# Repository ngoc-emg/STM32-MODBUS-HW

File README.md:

# STM32-MODBUS-HW
STM32-MODBUS HW

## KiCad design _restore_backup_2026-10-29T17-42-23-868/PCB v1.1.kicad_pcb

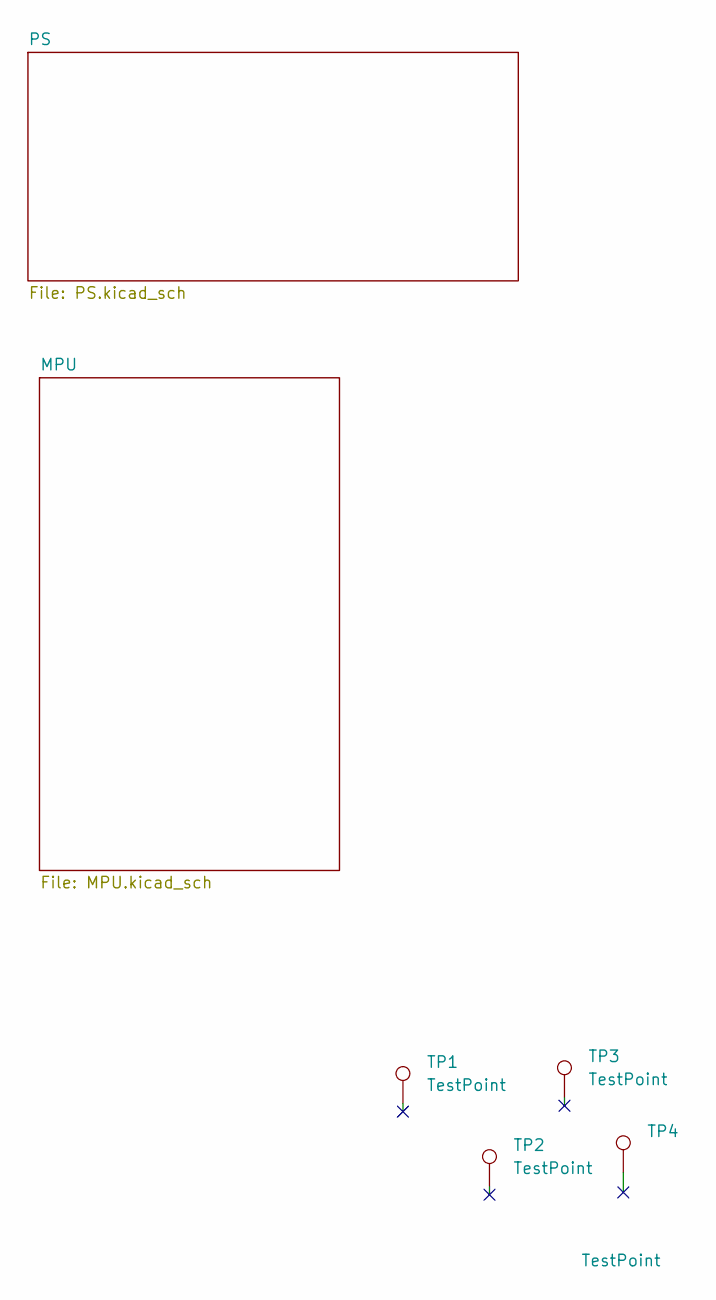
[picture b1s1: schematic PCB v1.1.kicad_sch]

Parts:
TP1, TP2, TP3, TP4: TestPoint; TestPoint_Plated_Hole_D4.0mm

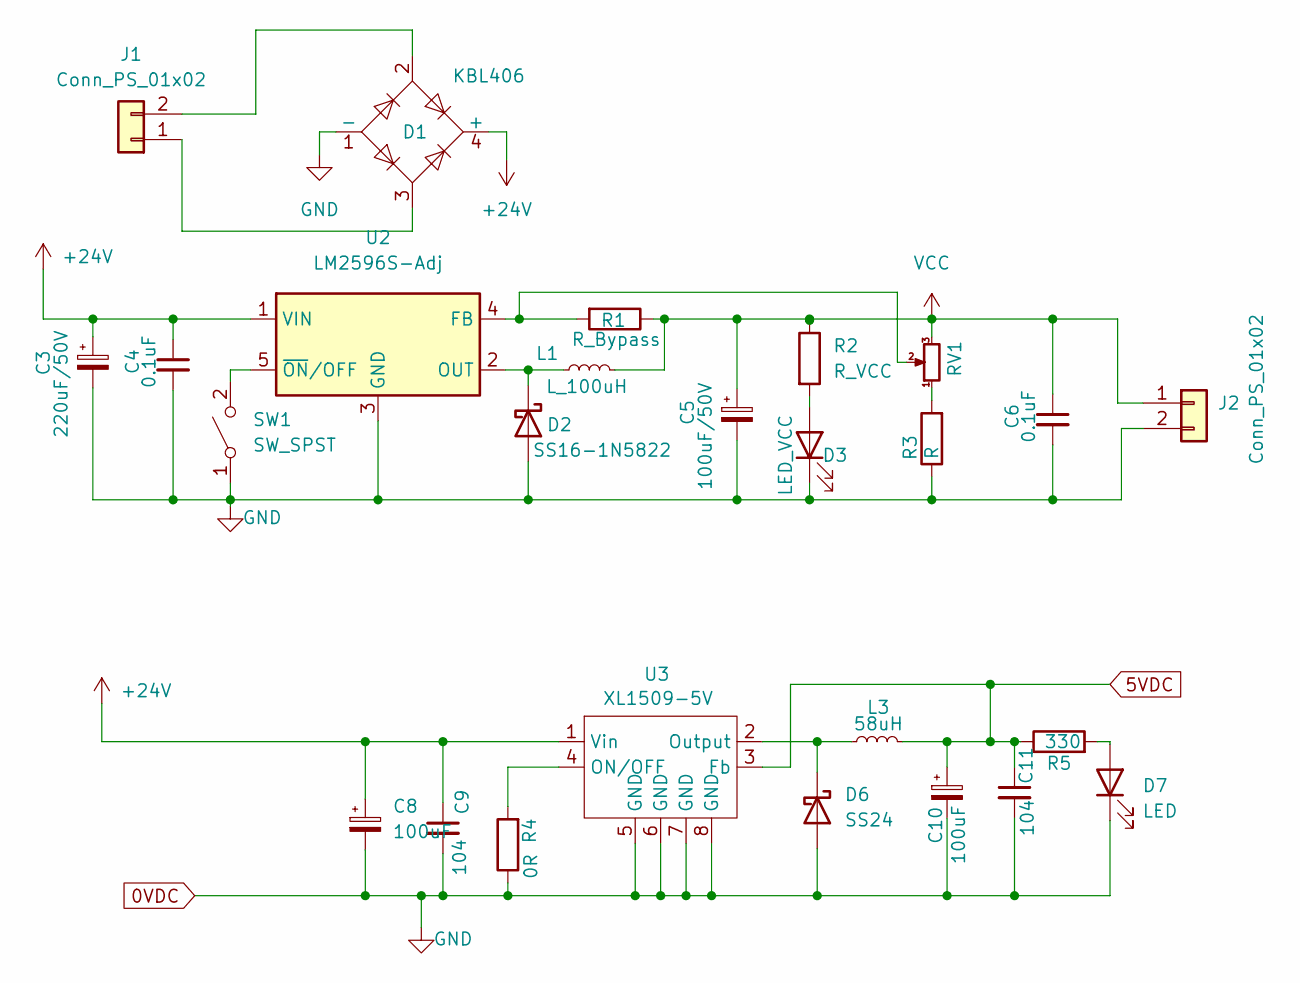
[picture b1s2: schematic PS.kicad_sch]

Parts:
C3: 220uF/50V; CP_Radial_D8.0mm_P3.80mm
C4, C6: 0.1uF; C_0805_2012Metric_Pad1.18x1.45mm_HandSolder
C5: 100uF/50V; CP_Radial_D8.0mm_P3.80mm
C8, C10: 100uF; CP_Radial_D8.0mm_P3.80mm
C9, C11: 104; C_0805_2012Metric_Pad1.18x1.45mm_HandSolder
D1: KBL406; Diode_Bridge_Vishay_GBU
D2: SS16-1N5822; D_DO-201AD_P5.08mm_Vertical_AnodeUp
D3: LED_VCC; LED_0805_2012Metric_Pad1.15x1.40mm_HandSolder
D6: SS24; D_SMA_Handsoldering
D7: LED; LED_0805_2012Metric_Pad1.15x1.40mm_HandSolder
J1, J2: Conn_PS_01x02; TerminalBlock_bornier-2_P5.08mm
L1: L_100uH; L_Toroid_Vertical_L14.7mm_W8.6mm_P5.58mm_Pulse_KM-1
L3: 58uH; L_Radial_D12.0mm_P6.00mm_Murata_1900R
R1: R_Bypass; R_0805_2012Metric_Pad1.20x1.40mm_HandSolder
R2: R_VCC; R_0805_2012Metric_Pad1.20x1.40mm_HandSolder
R3: R; R_0805_2012Metric_Pad1.20x1.40mm_HandSolder
R4: 0R; R_0805_2012Metric_Pad1.20x1.40mm_HandSolder
R5: 330; R_0805_2012Metric_Pad1.20x1.40mm_HandSolder
RV1: R_Potentiometer_Small; Potentiometer_Bourns_3296W_Vertical
SW1: SW_SPST; R_0805_2012Metric
U2: LM2596S-Adj; TO-263-5_TabPin3
U3: XL1509-5V; SOP-8_3.76x4.96mm_P1.27mm

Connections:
0VDC: C3.2, C4.2, C5.2, C6.2, C8.2, C9.2, C10.2, C11.2, D1.1 (-), D2.2 (A), D3.1 (K), D6.2 (A), D7.1 (K), J2.2, R3.1, R4.1, SW1.1 (A), U2.3 (GND), U3.5 (GND), U3.6 (GND), U3.7 (GND), U3.8 (GND); also elsewhere on the board
5VDC: C10.1, C11.1, L3.2, R5.1, U3.3 (Fb); also elsewhere on the board
+24V: C3.1, C4.1, C8.1, C9.1, D1.4 (+), U2.1 (VIN), U3.1 (Vin)
unnamed: D1.2, J1.2
unnamed: D1.3, J1.1
unnamed: D2.1 (K), L1.1, U2.2 (OUT)
unnamed: D3.2 (A), R2.2
unnamed: D6.1 (K), L3.1, U3.2 (Output)
unnamed: D7.2 (A), R5.2
unnamed: R1.2, RV1.2, U2.4 (FB)
unnamed: R3.2, RV1.1
unnamed: R4.2, U3.4 (ON/OFF)
unnamed: SW1.2 (B), U2.5 (~ON/OFF)
VCC: C5.1, C6.1, J2.1, L1.2, R1.1, R2.1, RV1.3; also elsewhere on the board

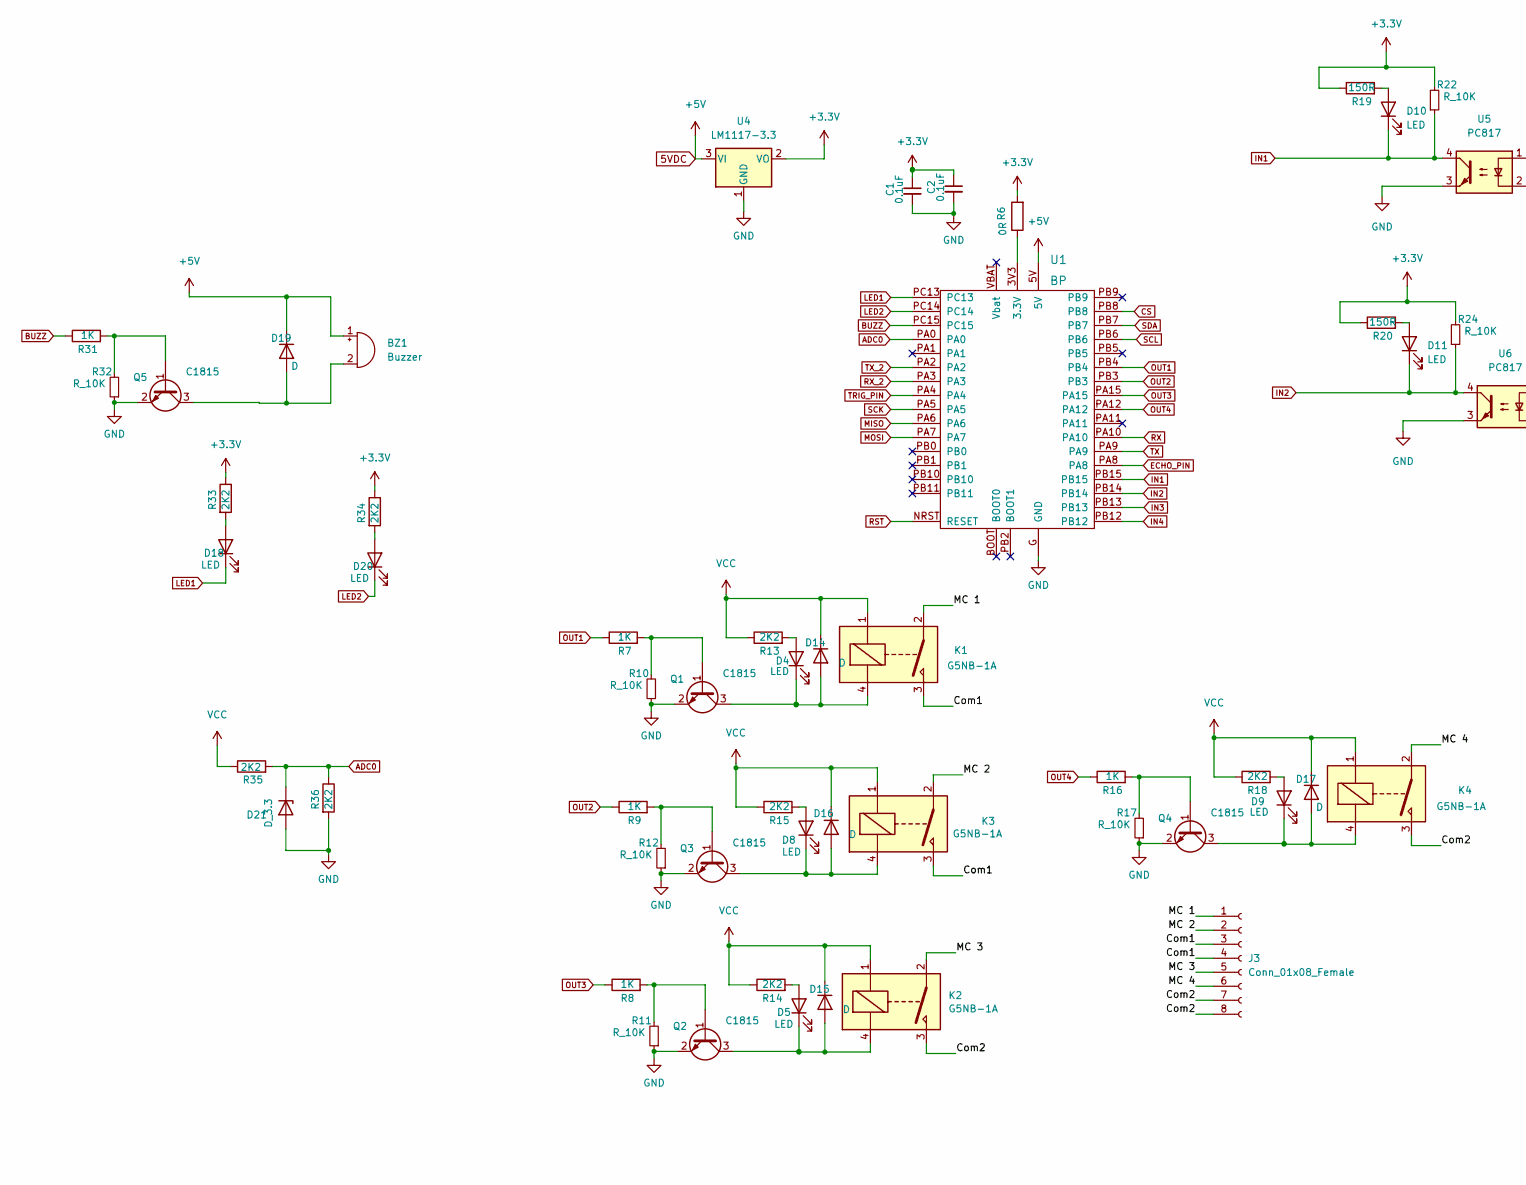
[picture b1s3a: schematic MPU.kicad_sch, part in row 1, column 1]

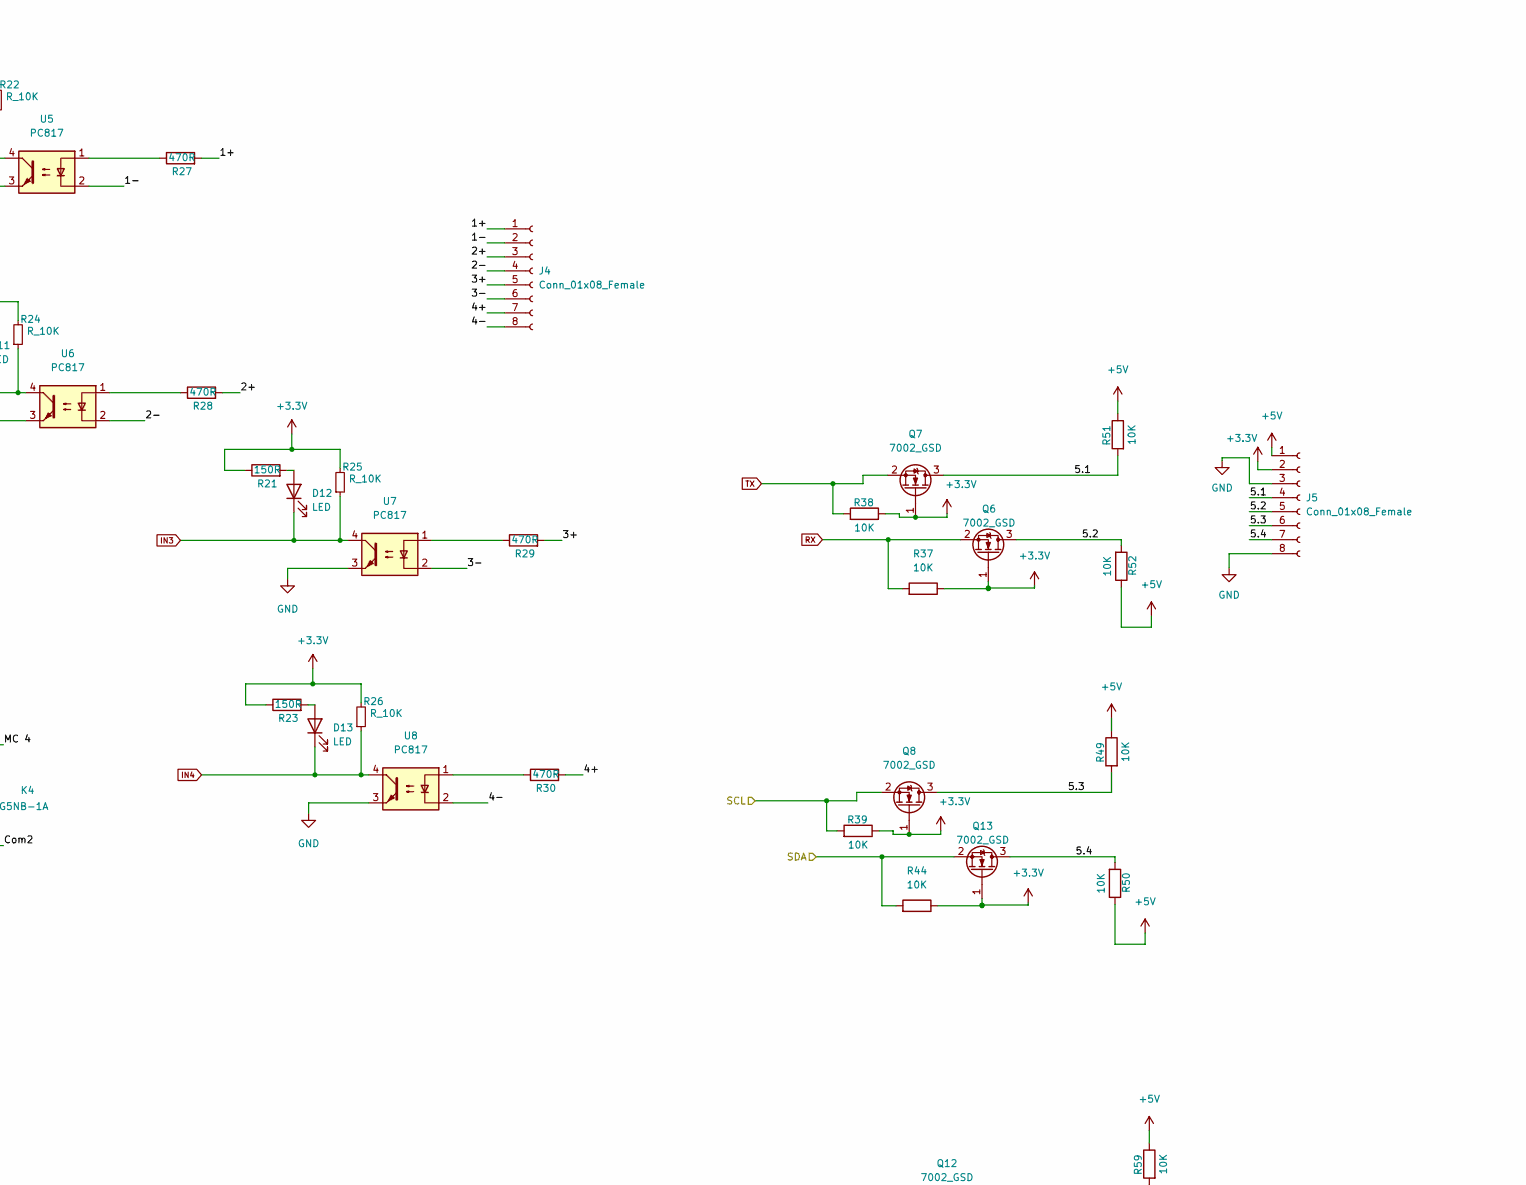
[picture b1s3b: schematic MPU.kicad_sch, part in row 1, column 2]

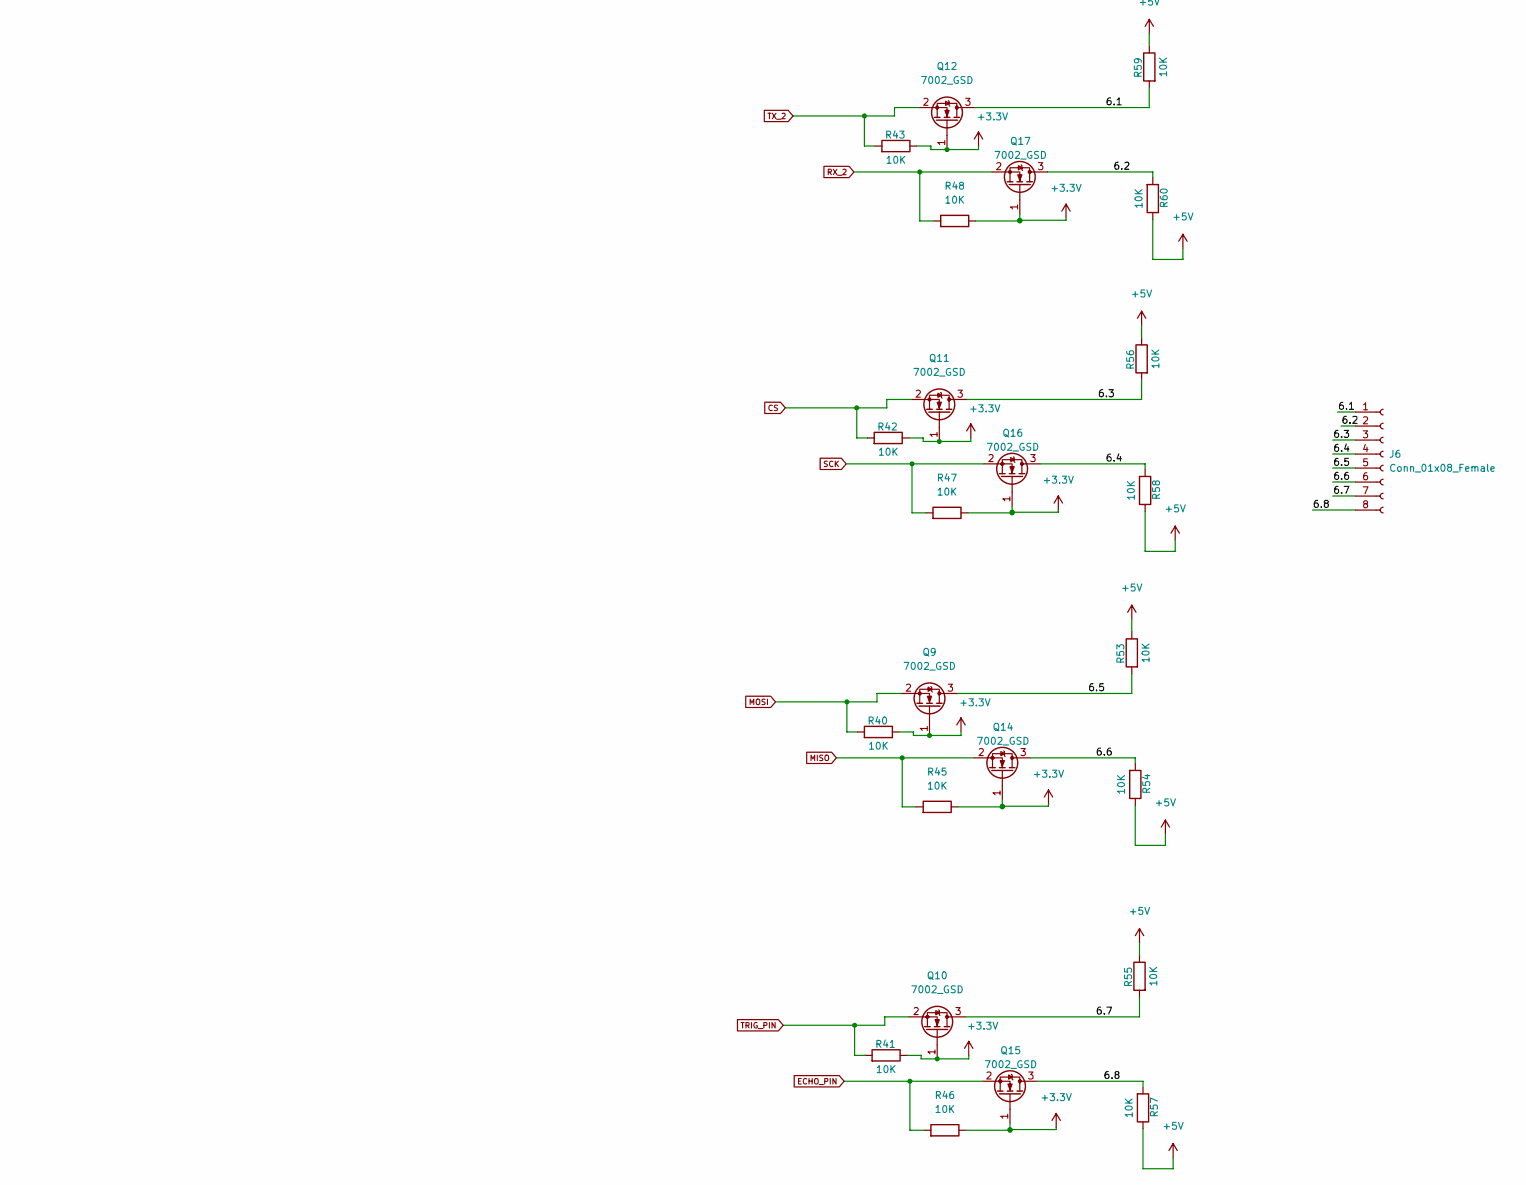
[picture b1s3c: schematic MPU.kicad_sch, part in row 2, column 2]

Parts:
BZ1: Buzzer; buzz _6.5
C1, C2: 0.1uF; C_0805_2012Metric_Pad1.18x1.45mm_HandSolder
D4, D5, D8, D9, D10, D11, D12, D13, D18, D20: LED; LED_0805_2012Metric_Pad1.15x1.40mm_HandSolder
D14, D15, D16, D17, D19: D; D_SMA
D21: D_3.3; D_2114_3652Metric
J3, J4, J5, J6: Conn_01x08_Female; TE_826576-8_1x08_P3.96mm_Vertical
K1, K2, K3, K4: G5NB-1A
Q1, Q2, Q3, Q4, Q5: C1815; SOT-23
Q6, Q7, Q8, Q9, Q10, Q11, Q12, Q13, Q14, Q15, Q16, Q17: 7002_GSD; SOT-23
R6: 0R; R_0805_2012Metric_Pad1.20x1.40mm_HandSolder
R7, R8, R9, R16, R31: 1K; R_0805_2012Metric_Pad1.20x1.40mm_HandSolder
R10, R11, R12, R17, R22, R24, R25, R26, R32: R_10K; R_0805_2012Metric_Pad1.20x1.40mm_HandSolder
R13, R14, R15, R18, R33, R34, R35, R36: 2K2; R_0805_2012Metric_Pad1.20x1.40mm_HandSolder
R19, R20, R21, R23: 150R; R_0805_2012Metric_Pad1.20x1.40mm_HandSolder
R27, R28, R29, R30: 470R; R_0805_2012Metric_Pad1.20x1.40mm_HandSolder
R37, R38, R39, R40, R41, R42, R43, R44, R45, R46, R47, R48, R49, R50, R51, R52, R53, R54, R55, R56, R57, R58, R59, R60: 10K; R_0805_2012Metric_Pad1.20x1.40mm_HandSolder
U1: BP; blue_pill
U4: LM1117-3.3; AMS1117
U5, U6, U7, U8: PC817

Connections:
0VDC: C1.2, C2.2, D21.2 (A), J5.3, J5.8, Q1.2 (E), Q2.2 (E), Q3.2 (E), Q4.2 (E), Q5.2 (E), R10.1, R11.1, R12.1, R17.1, R32.1, R36.2, U1.G (GND), U4.1 (GND), U5.3, U6.3, U7.3, U8.3; also elsewhere on the board
5VDC: BZ1.1 (-), D19.1 (K), J5.1, R49.1, R50.1, R51.1, R52.1, R53.1, R54.1, R55.1, R56.1, R57.1, R58.1, R59.1, R60.1, U1.5V, U4.3 (VI); also elsewhere on the board
+3V3: C1.1, C2.1, J5.2, Q6.1 (G), Q7.1 (G), Q8.1 (G), Q9.1 (G), Q10.1 (G), Q11.1 (G), Q12.1 (G), Q13.1 (G), Q14.1 (G), Q15.1 (G), Q16.1 (G), Q17.1 (G), R6.2, R19.1, R20.1, R21.1, R22.2, R23.1, R24.2, R25.2, R26.2, R33.1, R34.1, R37.1, R38.1, R39.1, R40.1, R41.1, R42.1, R43.1, R44.1, R45.1, R46.1, R47.1, R48.1, U4.2 (VO)
/MPU/1+: J4.1, R27.2
/MPU/1-: J4.2, U5.2
/MPU/2+: J4.3, R28.2
/MPU/2-: J4.4, U6.2
/MPU/3+: J4.5, R29.2
/MPU/3-: J4.6, U7.2
/MPU/4+: J4.7, R30.2
/MPU/4-: J4.8, U8.2
/MPU/5.1: J5.4, Q7.3 (D), R51.2
/MPU/5.2: J5.5, Q6.3 (D), R52.2
/MPU/5.3: J5.6, Q8.3 (D), R49.2
/MPU/5.4: J5.7, Q13.3 (D), R50.2
/MPU/6.1: J6.1, Q12.3 (D), R59.2
/MPU/6.2: J6.2, Q17.3 (D), R60.2
/MPU/6.3: J6.3, Q11.3 (D), R56.2
/MPU/6.4: J6.4, Q16.3 (D), R58.2
/MPU/6.5: J6.5, Q9.3 (D), R53.2
/MPU/6.6: J6.6, Q14.3 (D), R54.2
/MPU/6.7: J6.7, Q10.3 (D), R55.2
/MPU/6.8: J6.8, Q15.3 (D), R57.2
/MPU/Com1: J3.3, J3.4, K1.3, K3.3
/MPU/Com2: J3.7, J3.8, K2.3, K4.3
/MPU/MC 1: J3.1, K1.2
/MPU/MC 2: J3.2, K3.2
/MPU/MC 3: J3.5, K2.2
/MPU/MC 4: J3.6, K4.2
ADC0: D21.1 (K), R35.2, R36.1, U1.PA0
BUZZ: R31.1, U1.PC15
CS: Q11.2 (S), R42.2, U1.PB8
ECHO_PIN: Q15.2 (S), R46.2, U1.PA8
IN1: D10.1 (K), R22.1, U1.PB15, U5.4
IN2: D11.1 (K), R24.1, U1.PB14, U6.4
IN3: D12.1 (K), R25.1, U1.PB13, U7.4
IN4: D13.1 (K), R26.1, U1.PB12, U8.4
LED1: D18.1 (K), U1.PC13
LED2: D20.1 (K), U1.PC14
MISO: Q14.2 (S), R45.2, U1.PA6
MOSI: Q9.2 (S), R40.2, U1.PA7
unnamed: BZ1.2 (+), D19.2 (A), Q5.3 (C)
unnamed: D4.2 (A), R13.2
unnamed: D5.2 (A), R14.2
unnamed: D8.2 (A), R15.2
unnamed: D9.2 (A), R18.2
unnamed: D10.2 (A), R19.2
unnamed: D11.2 (A), R20.2
unnamed: D12.2 (A), R21.2
unnamed: D13.2 (A), R23.2
unnamed: D4.1 (K), D14.2 (A), K1.4, Q1.3 (C)
unnamed: D5.1 (K), D15.2 (A), K2.4, Q2.3 (C)
unnamed: D8.1 (K), D16.2 (A), K3.4, Q3.3 (C)
unnamed: D9.1 (K), D17.2 (A), K4.4, Q4.3 (C)
unnamed: D18.2 (A), R33.2
unnamed: D20.2 (A), R34.2
unnamed: Q1.1 (B), R7.2, R10.2
unnamed: Q2.1 (B), R8.2, R11.2
unnamed: Q3.1 (B), R9.2, R12.2
unnamed: Q4.1 (B), R16.2, R17.2
unnamed: Q5.1 (B), R31.2, R32.2
unnamed: R6.1, U1.3V3 (3.3V)
unnamed: R27.1, U5.1
unnamed: R28.1, U6.1
unnamed: R29.1, U7.1
unnamed: R30.1, U8.1
OUT1: R7.1, U1.PB4
OUT2: R9.1, U1.PB3
OUT3: R8.1, U1.PA15
OUT4: R16.1, U1.PA12
RST: U1.NRST (RESET)
RX: Q6.2 (S), R37.2, U1.PA10
RX_2: Q17.2 (S), R48.2, U1.PA3
SCK: Q16.2 (S), R47.2, U1.PA5
SCL: Q8.2 (S), R39.2, U1.PB6
SDA: Q13.2 (S), R44.2, U1.PB7
TRIG_PIN: Q10.2 (S), R41.2, U1.PA4
TX: Q7.2 (S), R38.2, U1.PA9
TX_2: Q12.2 (S), R43.2, U1.PA2
VCC: D14.1 (K), D15.1 (K), D16.1 (K), D17.1 (K), K1.1, K2.1, K3.1, K4.1, R13.1, R14.1, R15.1, R18.1, R35.1; also elsewhere on the board

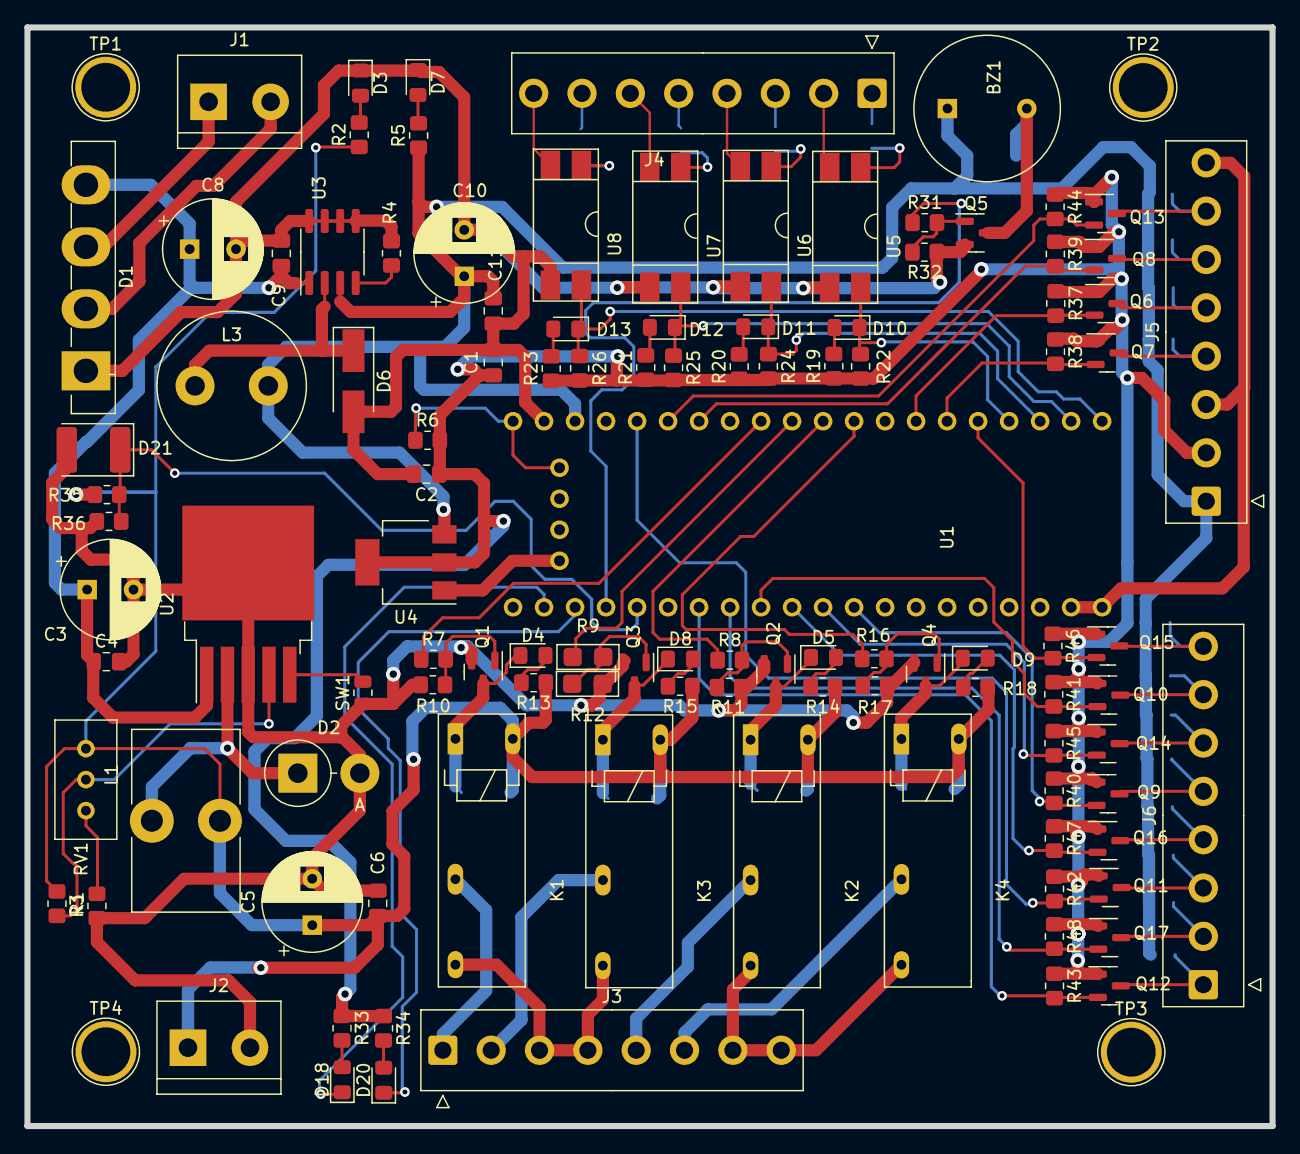
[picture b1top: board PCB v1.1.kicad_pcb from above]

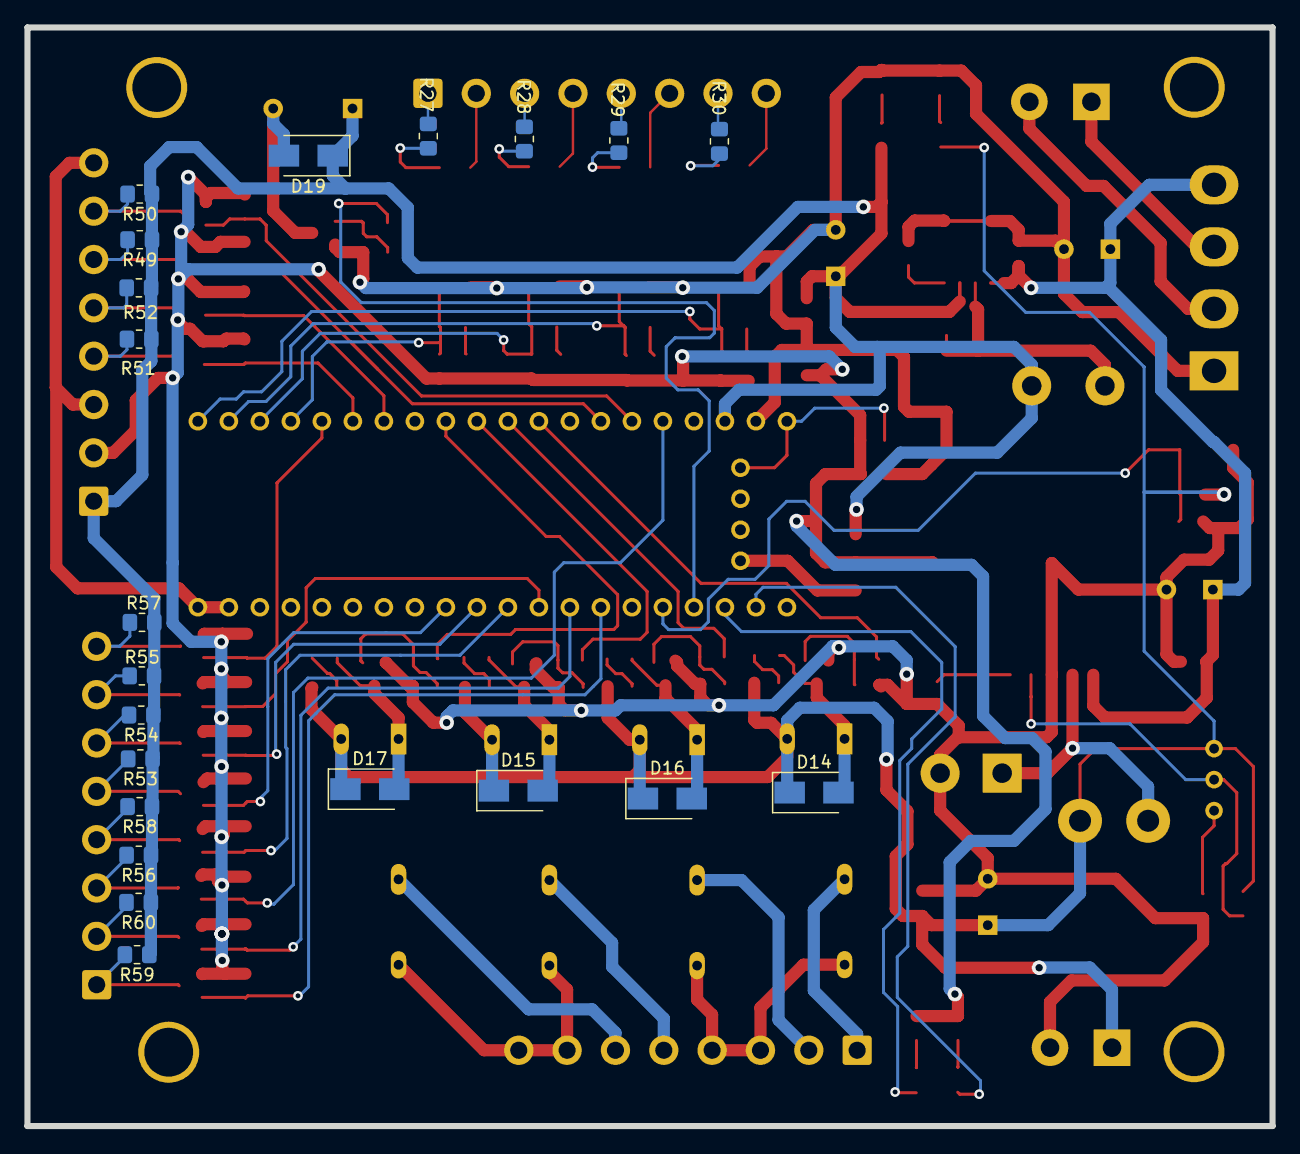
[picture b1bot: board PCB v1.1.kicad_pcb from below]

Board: 2 copper layers, 102.0 x 90.0 mm, 135 parts (21 on the bottom side), 90 nets.
